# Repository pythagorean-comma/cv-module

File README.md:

# cv-module

Per-string CV generation for a six-string guitar effects box: six analogue VCAs
(SSI2164) set per-string levels, and the audio never enters the digital domain.

The module hangs off the six `RV{n}01` level-control positions of
[`summing-mixer`](../summing-mixer), replacing its per-channel trimmers. That
board is **fabricated**, so this repo consumes its interface at a pinned commit
and never writes to it — see [`contract/PINNED.md`](contract/PINNED.md).

```
6 x Nu capsule -> Nexus-GK -> summing-mixer ---- RV{n}01 socket ---- [this]
                                    ^                                  |
                                    +------------ SIN{n} --------------+
```

## Status

Green end to end. `verify.py` passes, `test_verify.py` catches all 112 planted
faults, DRC is at zero, no net is unrouted, and the fabrication package is
written.

| | |
|---|---|
| netlist | 290 parts, 185 nets, 825 pin connections |
| schematic | 0 merges, 0 breaks, 0 stranded pins; ERC clean, `ERC_ALLOWED` empty |
| board | 106.9 × 233.5 mm, 4 layers. 5114 segments, 1142 vias, one track width (0.2 mm), one via size (0.7/0.3), no signal copper on either reference plane |
| routing | every millimetre by KiCadRoutingTools via `krt.py` |
| section 5 constraints | checked mechanically; see `docs/constraints.md` |
| fixings | six, derived from `placement.mounting_deflection()`, each in a plane void |
| silkscreen | title block, connector legend generated from the netlist, 274 designators |
| fabrication package | `fab/` — 9 gerbers, drill, job file, CPL, `ORDER.md` |
| deferred blocks | none. `design.DEFERRED` and `design.UNSPECIFIED` are both empty |

Documents to look at: the [schematic](docs/cv-module-schematic.pdf), the
[layout](docs/cv-module-layout.pdf) one page per copper layer, and a
[render](docs/cv-module-top.png).

**Caveats worth knowing before ordering.** One capacitor is genuinely short on DC
bias — `C840` gives 1.65 µF at 12 V against TI's "2.2 µF or higher" and wants a
higher-voltage part in the same 1210 land. Three Murata lines have no bias curve
here and are reported unchecked. And no check in this repo opens a datasheet: the
netlist comparison is pad number against pin number, so a wrong package passes
everything — see [`footprint-audit.md`](docs/footprint-audit.md), which caught
three.

## Run it

Nothing to install. Stdlib only, following the mixer's own rule that "there is
no `requirements.txt` because there is nothing to install". KiCad 10 is not
optional: `verify.py` runs `kicad-cli` twice, `gen_pcb.py` needs its bundled
Python for `pcbnew`, and `gen_plots.py` plots the schematic, layout and render.

```bash
./build.sh
```

Regenerates the netlist, schematic, project, BOM, generated docs, plots and the
fabrication package, then verifies the board on disk. It never writes the board.
It checks for KiCad first and stops if it is missing; it does not check for
KiCadRoutingTools, because `krt.py` is not one of its stages.

### The three things that do write the board

None of these is in `build.sh`:

```bash
python3 gen_pcb.py --discard-routing   # place, pour and stitch, from nothing
python3 krt.py                         # route it; --commit keeps the result
python3 returns.py                     # add ground stitches; --commit writes
```

`gen_pcb.py` destroys all signal copper. It writes a fresh board with the
footprints placed and the planes poured and nothing else — use it to start again
from nothing, never to make a change. It refuses without `--discard-routing`.

`krt.py` writes a candidate, `out/cv-module-krt.kicad_pcb`; only `--commit`
touches the tracked board. Scope decides what it destroys: `--nets "ENVA*"`
re-lays those six and leaves the rest alone, a bare `python3 krt.py` re-lays
every net.

`returns.py` only adds ground stitches, so it cannot destroy anything. Re-run it
after any re-route. `mounts.py` and `silk.py` are the same shape.

**To move a netlist change onto the routed board**, use KiCad's **Tools → Update
PCB from Schematic** against `out/cv-module.kicad_sch`, which `build.sh`
regenerates. That is the only sync path.

### Toolchain notes

`krt.py` is the one thing here that is not stdlib-only, and it is a subprocess
for that reason — the tool needs numpy, scipy and shapely. Give it an interpreter
of its own, `~/code/KiCadRoutingTools/krt-venv` or `$KRT_PYTHON`; it refuses with
instructions if it cannot find one. See
[`routing-tool.md`](docs/routing-tool.md#installing-the-tools-dependencies).

`gen_pcb.py` re-runs itself under KiCad's bundled interpreter, because `pcbnew`
is a SWIG extension that exists nowhere else, then re-runs `gen_project.py` —
`SaveBoard()` rewrites the project file with KiCad's defaults and takes every
design rule with it.

`contract/socket.py` finds the mixer at `$SUMMING_MIXER`, then
`../summing-mixer`, then `~/code/summing-mixer`. **Keep the two as siblings,
never nested** — and never run `git` from a directory containing both.

## What this repo takes from the mixer, and what it does not

The mixer is a fabricated hardware interface this module references. Referencing
an interface does not mean importing another project's Python:

| | |
|---|---|
| **the interface** — `design.py`, `source.py`, `fab/mechanical-*.json` | read at the pinned commit through `contract/socket.py`, with `git show`. Never copied |
| **the KiCad plumbing** — `sexp` `kisch` `symlib` `kicad` `kisim` | copied into [`toolchain/`](toolchain/PROVENANCE.md). Ours, and modifiable |

The mixer's root is never on `sys.path`. `delta.py` expresses this module's
effect as a delta against the mixer's *own* model, which only works while that
model is the mixer's and not a fork of it.

## What is where

`CLAUDE.md` carries the working rules and the full repo layout. In short:
`design.py` holds the values, derivations and netlist; `verify.py` checks them
against KiCad's own export and `test_verify.py` proves those checks can fail;
`constraints.py` and `delta.py` ask whether the constraints have mechanisms and
what this module costs the existing design; `placement.py`, `krt.py`,
`returns.py`, `mounts.py` and `silk.py` are the board. `docs/` is what a person
reads; `out/` is what another tool reads; `fab/` is what a fabricator is given.

## Open

1. **`MEASURED["noise_floor"]`** — a meter on the mixer's mono output, and the
   only one of the three measurements that can be taken before this board
   exists. It is the most load-bearing unknown here: across its declared range
   the module costs **0.01 dB or 0.79 dB quiescent, 0.08 dB or 3.13 dB while the
   lead feature runs**. It also gates a component value — below 81 µV, `R_IN`
   should move from 12k1 to 7.5 kΩ. [`bench.md`](docs/bench.md).

2. **`MEASURED["mcu_dcdc_efficiency"]` and `["pico_smps_efficiency"]`** — two
   ammeters after fabrication. Confirmations rather than gates: floors of 53 %
   and 45 % against declared ranges starting at 75 and 86. Note that the board
   has no provision for the first — `VA_RAW` has no series element at U22's VIN,
   so that measurement needs a lifted pin or a fitted 0 Ω link. The second is
   free: `D806` is already in series with `VSYS`.

3. **The order form.** `fab/ORDER.md` lists what is not derivable from anything
   here: surface finish, mask and silkscreen colour, electrical test,
   panelisation, IPC class, quantity.

4. **Fiducials and test pads** — not fitted. Three fiducials are derived and
   costed; the test-point case is that no analogue rail and not `MAGND` itself
   has any probe point on the board.

5. **The south-east corner** is 57 mm from its nearest fixing and carries the
   USB socket. Grow the board, move the module, or accept it — all three are
   decisions, so `placement.mounting_reach()` reports the distance rather than
   taking one.

6. **Review the copper.** 844 router vias against an earlier seed's 595 is 33 %
   more perforations of both reference planes for 9.8 % less track. No check
   grades that trade. The recommendation is about scope: re-route a region, not
   the board.

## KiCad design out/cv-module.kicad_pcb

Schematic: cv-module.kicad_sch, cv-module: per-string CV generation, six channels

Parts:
C101, C201, C301, C401, C501, C601, C802, C814: 10u/16V X7R; C_1210_3225Metric
C102, C152, C202, C252, C302, C352, C402, C452, C502, C552, C602, C652: 1200p/50V C0G; C_0805_2012Metric
C121, C221, C321, C421, C521, C621: 100p/50V C0G; C_0805_2012Metric
C131, C231, C331, C431, C531, C631: 150n/50V X7R; C_0805_2012Metric
C141, C241, C341, C441, C541, C641: 56n/50V X7R; C_0805_2012Metric
C142, C242, C342, C442, C542, C642: 22n/50V X7R; C_0805_2012Metric
C151, C251, C351, C451, C551, C651, C810: 470n/50V X7R; C_0805_2012Metric
C701, C702, C703, C704, C705, C706, C707, C708, C709, C710, C711, C712, C713, C714, C715, C716, C717, C718, C719, C720, C721, C722, C723, C724, C803, C809, C817, C818, C819, C835, C836, C837, C838, C841, C842: 100n/50V X7R; C_0805_2012Metric
C801: 100n/50V C0G; C_0805_2012Metric
C805: 2n2/50V C0G; C_0805_2012Metric
C806, C815, C816: 1u/16V X7R; C_0805_2012Metric
C807, C808, C811, C812, C813: 10u/50V X7R; C_1210_3225Metric
C840: 2u2/50V X7R; C_1210_3225Metric
C843: 22u/16V X5R; C_1210_3225Metric
D151, D152, D251, D252, D351, D352, D451, D452, D551, D552, D651, D652, D805: 1N4148W; D_SOD-123
D801, D802, D813, D823, D833: BAT54; D_SOD-123
D803, D806: PMEG2010AEH; D_SOD-123F
D804: B340A; D_SMA
F801: 1.6A T 250V; Fuse_Schurter_UMT250
J1: CH1; PinHeader_1x02_P2.54mm_Vertical
J2: CH2; PinHeader_1x02_P2.54mm_Vertical
J3: CH3; PinHeader_1x02_P2.54mm_Vertical
J4: CH4; PinHeader_1x02_P2.54mm_Vertical
J5: CH5; PinHeader_1x02_P2.54mm_Vertical
J6: CH6; PinHeader_1x02_P2.54mm_Vertical
J7: BOND; TestPoint_Pad_D2.0mm
J8: PWR; PinHeader_1x02_P2.54mm_Vertical
J15: MIDIIN; PinHeader_1x03_P2.54mm_Vertical
J16: MIDIOUT; PinHeader_1x03_P2.54mm_Vertical
J17: TAP; PinHeader_1x02_P2.54mm_Vertical
J18: EXPR; PinHeader_1x03_P2.54mm_Vertical
J19: RESET; PinHeader_1x02_P2.54mm_Vertical
K801, K802, K803: DPDT
L801: 744222; L_CommonMode_Wuerth_WE-SL2
L802: 15u 20%; L_Bourns_SRN6045TA
Q801: DMG1012T; SOT-523
R101, R102, R201, R202, R301, R302, R401, R402, R501, R502, R601, R602, R801, R802: 10k 0.1%; R_0805_2012Metric
R111, R121, R211, R221, R311, R321, R411, R421, R511, R521, R611, R621: 12k1 0.1%; R_0805_2012Metric
R115, R215, R315, R415, R515, R615: 220R 1%; R_0805_2012Metric
R131, R132, R231, R232, R331, R332, R431, R432, R531, R532, R631, R632: 1M 1%; R_0805_2012Metric
R141, R144, R156, R241, R244, R256, R341, R344, R356, R441, R444, R456, R541, R544, R556, R641, R644, R656: 22k 1%; R_0805_2012Metric
R142, R143, R242, R243, R342, R343, R442, R443, R542, R543, R642, R643: 17k8 1%; R_0805_2012Metric
R151, R152, R153, R155, R251, R252, R253, R255, R351, R352, R353, R355, R451, R452, R453, R455, R551, R552, R553, R555, R651, R652, R653, R655, R830: 10k 1%; R_0805_2012Metric
R154, R157, R254, R257, R354, R357, R454, R457, R554, R557, R654, R657: 4k99 1%; R_0805_2012Metric
R803, R811, R812, R813, R814, R815, R816: 100k 1%; R_0805_2012Metric
R804, R805: 4R7 1%; R_0805_2012Metric
R827: 390R 1%; R_0805_2012Metric
R828: 33R 5%; R_0805_2012Metric
R829: 10R 5%; R_0805_2012Metric
R831, R832, R833: 1k 1%; R_0805_2012Metric
R850: 88k7 1%; R_0805_2012Metric
R851: 22k1 1%; R_0805_2012Metric
R901, R902: 0R; R_0805_2012Metric
U1, U2, U3, U4, U5, U6, U7, U8: OPA1644; SOIC-14_3.9x8.7mm_P1.27mm
U9, U10: SSI2164; SOIC-16_3.9x9.9mm_P1.27mm
U11: 74AHC541; SOIC-20W_7.5x12.8mm_P1.27mm
U12: MAX6126A25; SOIC-8_3.9x4.9mm_P1.27mm
U13, U14: TL074; SOIC-14_3.9x8.7mm_P1.27mm
U15: TMR6-2422WI; TRACO_TMR-6-xxxxWI_Dual_THT
U16: NCP1117-5.0; TO-252-2
U17: MCP3564; TSSOP-20_4.4x6.5mm_P0.65mm
U18: MCP1700-3.3; SOT-23
U19: RaspberryPi_Pico; RaspberryPi_Pico_SMD_HandSolder
U21: TLP2761; SO-6L_10x3.84mm_P1.27mm
U22: TPS560430XF; SOT-23-6

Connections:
AGND: J7.1, R901.2
AOUT1: D151.2 (A), D152.1 (K), U13.1
AOUT2: D251.2 (A), D252.1 (K), U13.7
AOUT3: D351.2 (A), D352.1 (K), U13.8
AOUT4: D451.2 (A), D452.1 (K), U13.14
AOUT5: D551.2 (A), D552.1 (K), U14.1
AOUT6: D651.2 (A), D652.1 (K), U14.7
BUF1: C101.1, R102.2, R151.1, R153.1, U1.1
BUF2: C201.1, R202.2, R251.1, R253.1, U1.7
BUF3: C301.1, R302.2, R351.1, R353.1, U1.8
BUF4: C401.1, R402.2, R451.1, R453.1, U1.14
BUF5: C501.1, R502.2, R551.1, R553.1, U2.1
BUF6: C601.1, R602.2, R651.1, R653.1, U2.7
CPL1: C101.2, R111.1
CPL2: C201.2, R211.1
CPL3: C301.2, R311.1
CPL4: C401.2, R411.1
CPL5: C501.2, R511.1
CPL6: C601.2, R611.1
CS: U17.13 (CS), U19.22 (GPIO17)
CVN1: C142.1, R143.2, U7.2 (-)
CVN2: C242.1, R243.2, U7.6 (-)
CVN3: C342.1, R343.2, U7.9 (-)
CVN4: C442.1, R443.2, U7.13 (-)
CVN5: C542.1, R543.2, U8.2 (-)
CVN6: C642.1, R643.2, U8.6 (-)
CVX1: C141.1, R141.2, R142.1, R143.1, R144.2
CVX2: C241.1, R241.2, R242.1, R243.1, R244.2
CVX3: C341.1, R341.2, R342.1, R343.1, R344.2
CVX4: C441.1, R441.2, R442.1, R443.1, R444.2
CVX5: C541.1, R541.2, R542.1, R543.1, R544.2
CVX6: C641.1, R641.2, R642.1, R643.1, R644.2
ENV1: C151.2, R155.2, R156.1, U2.8
ENV2: C251.2, R255.2, R256.1, U2.14
ENV3: C351.2, R355.2, R356.1, U4.8
ENV4: C451.2, R455.2, R456.1, U4.14
ENV5: C551.2, R555.2, R556.1, U6.8
ENV6: C651.2, R655.2, R656.1, U6.14
ENVA1: C152.1, R156.2, R157.1, U17.5 (CH0)
ENVA2: C252.1, R256.2, R257.1, U17.6 (CH1)
ENVA3: C352.1, R356.2, R357.1, U17.7 (CH2)
ENVA4: C452.1, R456.2, R457.1, U17.8 (CH3)
ENVA5: C552.1, R556.2, R557.1, U17.10 (CH5)
ENVA6: C652.1, R656.2, R657.1, U17.11 (CH6)
ENVN1: C151.1, R153.2, R154.2, R155.1, U2.9 (-)
ENVN2: C251.1, R253.2, R254.2, R255.1, U2.13 (-)
ENVN3: C351.1, R353.2, R354.2, R355.1, U4.9 (-)
ENVN4: C451.1, R453.2, R454.2, R455.1, U4.13 (-)
ENVN5: C551.1, R553.2, R554.2, R555.1, U6.9 (-)
ENVN6: C651.1, R653.2, R654.2, R655.1, U6.13 (-)
EXPR: C838.1, R833.2, U19.31 (GPIO26_ADC0)
EXPRV: J18.2, R832.2
EXPRW: J18.1, R833.1
FEN1: R101.2, R102.1, U1.2 (-)
FEN2: R201.2, R202.1, U1.6 (-)
FEN3: R301.2, R302.1, U1.9 (-)
FEN4: R401.2, R402.1, U1.13 (-)
FEN5: R501.2, R502.1, U2.2 (-)
FEN6: R601.2, R602.1, U2.6 (-)
FSAC: C805.2, D801.1 (K), D802.2 (A)
FSD: D813.2 (A), D823.2 (A), D833.2 (A), K801.12, K802.12, K803.12, Q801.3 (D)
FSDRV: C805.1, U19.20 (GPIO15)
FSG: C806.1, D802.1 (K), Q801.1 (G), R803.1
HW1: D152.2 (A), R152.2, R154.1
HW2: D252.2 (A), R252.2, R254.1
HW3: D352.2 (A), R352.2, R354.1
HW4: D452.2 (A), R452.2, R454.1
HW5: D552.2 (A), R552.2, R554.1
HW6: D652.2 (A), R652.2, R654.1
HWN1: D151.1 (K), R151.2, R152.1, U13.2 (-)
HWN2: D251.1 (K), R251.2, R252.1, U13.6 (-)
HWN3: D351.1 (K), R351.2, R352.1, U13.9 (-)
HWN4: D451.1 (K), R451.2, R452.1, U13.13 (-)
HWN5: D551.1 (K), R551.2, R552.1, U14.2 (-)
HWN6: D651.1 (K), R651.2, R652.1, U14.6 (-)
IGND: C807.2, C808.2, C809.2, C810.1, L801.3, U15.1 (-Vin), U15.3 (Remote)
IGND_J: J8.2, L801.2
IIN1: R111.2, R115.1, U9.2 (I_IN1)
IIN2: R211.2, R215.1, U9.7 (I_IN2)
IIN3: R311.2, R315.1, U9.10 (I_IN3)
IIN4: R411.2, R415.1, U10.2 (I_IN1)
IIN5: R511.2, R515.1, U10.7 (I_IN2)
IIN6: R611.2, R615.1, U10.10 (I_IN3)
IOUT1: C121.1, R121.1, R132.2, U3.2 (-), U9.4 (I_OUT1)
IOUT2: C221.1, R221.1, R232.2, U3.6 (-), U9.5 (I_OUT2)
IOUT3: C321.1, R321.1, R332.2, U3.9 (-), U9.12 (I_OUT3)
IOUT4: C421.1, R421.1, R432.2, U3.13 (-), U10.4 (I_OUT1)
IOUT5: C521.1, R521.1, R532.2, U4.2 (-), U10.5 (I_OUT2)
IOUT6: C621.1, R621.1, R632.2, U4.6 (-), U10.12 (I_OUT3)
IRQ: U17.17 (IRQ), U19.26 (GPIO20)
IVOUT1: C121.2, K801.8, R121.2, R131.1, U3.1
IVOUT2: C221.2, K801.5, R221.2, R231.1, U3.7
IVOUT3: C321.2, K802.8, R321.2, R331.1, U3.8
IVOUT4: C421.2, K802.5, R421.2, R431.1, U3.14
IVOUT5: C521.2, K803.8, R521.2, R531.1, U4.1
IVOUT6: C621.2, K803.5, R621.2, R631.1, U4.7
LOGO1: R141.1, U11.18 (Y0)
LOGO2: R241.1, U11.17 (Y1)
LOGO3: R341.1, U11.16 (Y2)
LOGO4: R441.1, U11.15 (Y3)
LOGO5: R541.1, U11.14 (Y4)
LOGO6: R641.1, U11.13 (Y5)
MAGND: C102.2, C141.2, C152.2, C202.2, C241.2, C252.2, C302.2, C341.2, C352.2, C402.2, C441.2, C452.2, C502.2, C541.2, C552.2, C602.2, C641.2, C652.2, C701.2, C702.2, C703.2, C704.2, C705.2, C706.2, C707.2, C708.2, C709.2, C710.2, C711.2, C712.2, C713.2, C714.2, C715.2, C716.2, C717.2, C718.2, C719.2, C720.2, C721.2, C722.2, C723.2, C724.2, C801.2, C802.2, C803.2, C815.2, C816.2, C817.2, C818.2, C819.2, D803.1 (K), R157.2, R257.2, R357.2, R457.2, R557.2, R657.2, R901.1, R902.1, U1.3 (+), U1.5 (+), U1.10 (+), U1.12 (+), U2.3 (+), U2.5 (+), U2.10 (+), U2.12 (+), U3.3 (+), U3.5 (+), U3.10 (+), U3.12 (+), U4.3 (+), U4.5 (+), U4.10 (+), U4.12 (+), U5.3 (+), U5.5 (+), U5.10 (+), U5.12 (+), U6.3 (+), U6.5 (+), U6.10 (+), U6.12 (+), U7.3 (+), U7.5 (+), U7.10 (+), U7.12 (+), U8.3 (+), U8.5 (+), U8.10 (+), U8.12 (+), U9.8 (GND), U9.13 (I_OUT4), U9.15 (I_IN4), U10.8 (GND), U10.13 (I_OUT4), U10.15 (I_IN4), U11.8 (A6), U11.9 (A7), U11.10 (GND), U12.3 (GND), U12.4 (GNDS), U13.3 (+), U13.5 (+), U13.10 (+), U13.12 (+), U14.3 (+), U14.5 (+), U14.10 (+), U14.12 (+), U17.2 (AGND), U17.3 (REFIN-), U17.9 (CH4), U17.12 (CH7), U17.19 (DGND), U18.1 (GND)
MCB: C842.1, U22.1 (CB)
MCLK: U17.18 (MCLK), U19.27 (GPIO21)
MDGND: C806.2, C810.2, C811.2, C812.2, C813.2, C814.2, C835.2, C836.2, C837.2, C838.2, C840.2, C841.2, C843.2, D801.2 (A), J16.2, J17.2, J18.3, J19.2, Q801.2 (S), R803.2, R811.2, R812.2, R813.2, R814.2, R815.2, R816.2, R851.2, R902.2, U15.7 (Com), U16.1 (GND), U19.3 (GND), U19.8 (GND), U19.13 (GND), U19.18 (GND), U19.23 (GND), U19.28 (GND), U19.33 (AGND), U19.38 (GND), U21.4 (GND), U22.2 (GND)
MFB: R850.2, R851.1, U22.3 (FB)
MIDI_RX: U19.17 (GPIO13), U21.5 (VO)
MIDI_TX: R829.1, U19.16 (GPIO12)
MINA: D805.1 (K), R827.2, U21.1 (A)
MINJ: J15.1, R827.1
MINK: D805.2 (A), J15.3, U21.3 (K)
MINSH: C836.1, J15.2
MISO: U17.16 (SDO), U19.21 (GPIO16)
MOSI: U17.15 (SDI), U19.25 (GPIO19)
MOUTD: J16.3, R829.2
MOUTV: J16.1, R828.2
MSW: C842.2, L802.1, U22.6 (SW)
OE: U11.1 (G1), U11.19 (G2), U19.19 (GPIO14)
PIN1: J1.1, K801.10, R101.1
PIN2: J2.1, K801.3, R201.1
PIN3: J3.1, K802.10, R301.1
PIN4: J4.1, K802.3, R401.1
PIN5: J5.1, K803.10, R501.1
PIN6: J6.1, K803.3, R601.1
PWM1: R811.1, U11.2 (A0), U19.1 (GPIO0)
PWM2: R812.1, U11.3 (A1), U19.4 (GPIO2)
PWM3: R813.1, U11.4 (A2), U19.6 (GPIO4)
PWM4: R814.1, U11.5 (A3), U19.9 (GPIO6)
PWM5: R815.1, U11.6 (A4), U19.11 (GPIO8)
PWM6: R816.1, U11.7 (A5), U19.14 (GPIO10)
RCJ1: C102.1, R115.2
RCJ2: C202.1, R215.2
RCJ3: C302.1, R315.2
RCJ4: C402.1, R415.2
RCJ5: C502.1, R515.2
RCJ6: C602.1, R615.2
RINV: R801.2, R802.1, U8.9 (-)
RUN: J19.1, U19.30 (RUN)
SCLK: U17.14 (SCK), U19.24 (GPIO18)
SIN1: J1.2, K801.9
SIN2: J2.2, K801.4
SIN3: J3.2, K802.9
SIN4: J4.2, K802.4
SIN5: J5.2, K803.9
SIN6: J6.2, K803.4
SPARE0: U8.13 (-), U8.14
SPARE1: U14.8, U14.9 (-)
SPARE2: U14.13 (-), U14.14
SRV1: C131.2, R132.1, U5.1
SRV2: C231.2, R232.1, U5.7
SRV3: C331.2, R332.1, U5.8
SRV4: C431.2, R432.1, U5.14
SRV5: C531.2, R532.1, U6.1
SRV6: C631.2, R632.1, U6.7
SVN1: C131.1, R131.2, U5.2 (-)
SVN2: C231.1, R231.2, U5.6 (-)
SVN3: C331.1, R331.2, U5.9 (-)
SVN4: C431.1, R431.2, U5.13 (-)
SVN5: C531.1, R531.2, U6.2 (-)
SVN6: C631.1, R631.2, U6.6 (-)
TAP: C837.1, R831.2, U19.29 (GPIO22)
TAPJ: J17.1, R830.2, R831.1
V3V3: C816.1, C817.1, C818.1, U17.1 (AVDD), U17.20 (DVDD), U18.2 (VO)
V5: C814.1, C815.1, U12.2 (IN), U16.2 (VO), U18.3 (VI)
VA+: C701.1, C703.1, C705.1, C707.1, C709.1, C711.1, C713.1, C715.1, C717.1, C719.1, C721.1, C723.1, C811.1, R804.2, U1.4 (V+), U2.4 (V+), U3.4 (V+), U4.4 (V+), U5.4 (V+), U6.4 (V+), U7.4 (V+), U8.4 (V+), U9.16 (V+), U10.16 (V+), U13.4 (V+), U14.4 (V+)
VA-: C702.1, C704.1, C706.1, C708.1, C710.1, C712.1, C714.1, C716.1, C718.1, C720.1, C722.1, C724.1, C812.1, R805.2, U1.11 (V-), U2.11 (V-), U3.11 (V-), U4.11 (V-), U5.11 (V-), U6.11 (V-), U7.11 (V-), U8.11 (V-), U9.9 (V-), U10.9 (V-), U13.11 (V-), U14.11 (V-)
VA_RAW: C813.1, C840.1, C841.1, R804.1, U15.6 (+Vout), U16.3 (VI), U22.4 (EN), U22.5 (VIN)
VC1: C142.2, R142.2, U7.1, U9.3 (VC1)
VC2: C242.2, R242.2, U7.7, U9.6 (VC2)
VC3: C342.2, R342.2, U7.8, U9.11 (VC3)
VC4: C442.2, R442.2, U7.14, U10.3 (VC1)
VC5: C542.2, R542.2, U8.1, U10.6 (VC2)
VC6: C642.2, R642.2, U8.7, U10.11 (VC3)
VIN: D804.2 (A), L801.4
VIN_F: F801.2, L801.1
VIN_J: F801.1, J8.1
VIN_P: C807.1, C808.1, C809.1, D804.1 (K), U15.2 (+Vin)
VMCU: C835.1, R828.1, R830.1, R832.1, U19.36 (3V3), U21.6 (VDD)
VMOD: C843.1, D806.2 (A), D813.1 (K), D823.1 (K), D833.1 (K), K801.1, K802.1, K803.1, L802.2, R850.1
VNR: C801.1, U12.1 (NR)
VN_RAW: R805.1, U15.8 (-Vout)
VREF: C802.1, C803.1, C819.1, R801.1, U11.20 (VCC), U12.6 (OUTS), U12.7 (OUTF), U17.4 (REFIN+)
VREFN: D803.2 (A), R144.1, R244.1, R344.1, R444.1, R544.1, R644.1, R802.2, U8.8
VSYS: D806.1 (K), U19.39 (VSYS)

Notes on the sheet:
The boundary runs through U11: A-side from the digital domain, Y-side precision analogue, GND on MAGND. See floorplan.py.
Fail-safe: any stuck MCU state collapses the pump, the FET releases, and de-energised is bypass. D803 covers the one path the pump cannot see. See design.fail_safe().
R901 is THE bond, to the mixer's TP6. R902 is internal. Constraint 2 allows exactly one of the first.
The isolation barrier runs through U15: pins 1-3 are referenced to IGND, which is the inlet's 0 V and the mixer's PGND through the shared jack; pins 6-8 to MDGND. C810 is the only other part that touches both. See design.barrier_return().
The envelope ADC. AGND and DGND are one net here and both are MAGND -- DS20006181C section 7.3's second scheme, and the only one compatible with this board having exactly one analogue/digital star. Six logic signals leave for the controller and no analogue trace crosses the boundary; MCLK is one of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
The controller. Three 3.3 V and 5 V nets on this sheet and no two of them are one: V3V3 is the ADC's, linear from V5; VMOD is U22's switched 5 V, carrying the module and the relay coils; VMCU is the module's own 3.3 V, made on it by an RT6150 out of VSYS and brought back out on pin 36. V5 is what i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

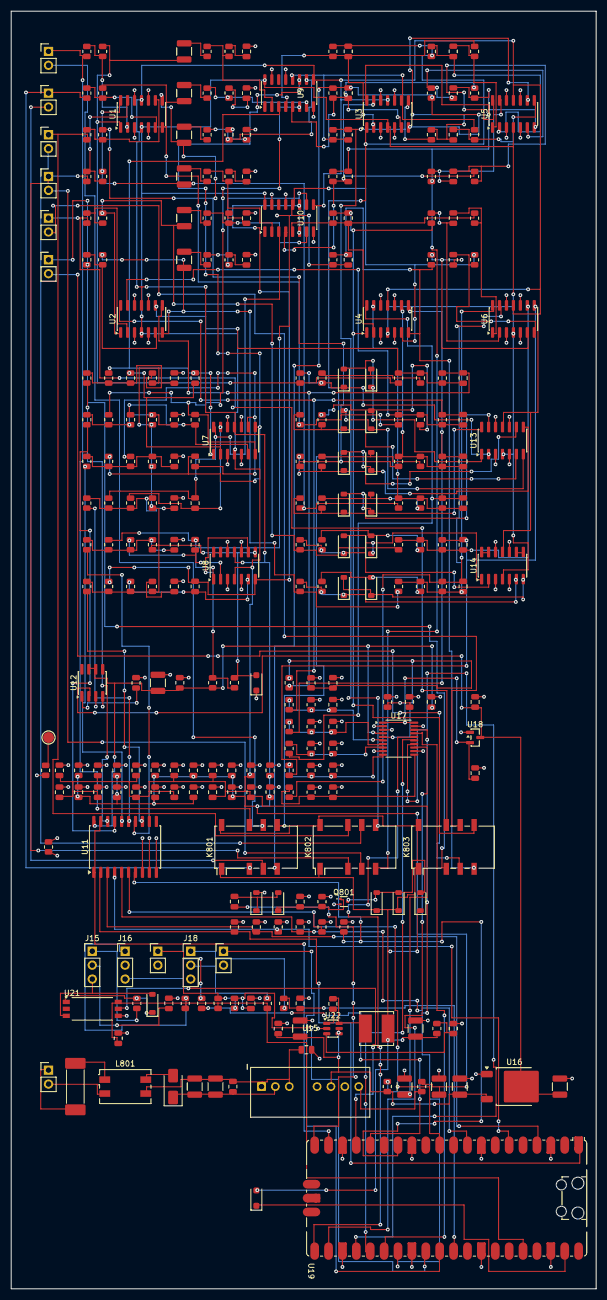
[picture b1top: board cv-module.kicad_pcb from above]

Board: 4 copper layers, 106.9 x 233.6 mm, 290 parts (0 on the bottom side), 185 nets.

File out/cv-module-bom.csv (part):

Reference,Value,Footprint,MPN,Fitted,Order,Unit low,Unit high,Currency,Qty break,Basis,Source
"C101,C201,C301,C401,C501,C601,C802,C814",10u/16V X7R,Capacitor_SMD:C_1210_3225Metric,GRM21BR61C106KE15L,8,12,0.08,0.25,GBP,25,band,"typical distributor band, not read this session"
"C102,C152,C202,C252,C302,C352,C402,C452,C502,C552,C602,C652",1200p/50V C0G,Capacitor_SMD:C_0805_2012Metric,GRM2165C1H122JA01D,12,16,0.02,0.08,GBP,100,band,"typical distributor band, not read this session"
"C121,C221,C321,C421,C521,C621",100p/50V C0G,Capacitor_SMD:C_0805_2012Metric,GRM2165C1H101JA01D,6,10,0.02,0.08,GBP,100,band,"typical distributor band, not read this session"
"C131,C231,C331,C431,C531,C631",150n/50V X7R,Capacitor_SMD:C_0805_2012Metric,GRM216R71H154KA01D,6,10,0.02,0.08,GBP,100,band,"typical distributor band, not read this session"
"C141,C241,C341,C441,C541,C641",56n/50V X7R,Capacitor_SMD:C_0805_2012Metric,GRM216R71H563KA01D,6,10,0.02,0.08,GBP,100,band,"typical distributor band, not read this session"
"C142,C242,C342,C442,C542,C642",22n/50V X7R,Capacitor_SMD:C_0805_2012Metric,GRM216R71H223KA01D,6,10,0.02,0.08,GBP,100,band,"typical distributor band, not read this session"
"C151,C251,C351,C451,C551,C651,C810",470n/50V X7R,Capacitor_SMD:C_0805_2012Metric,GRM21BR71H474KA88L,7,11,0.02,0.08,GBP,100,band,"typical distributor band, not read this session"
"C701,C702,C703,C704,C705,C706,C707,C708,C709,C710,C711,C712,C713,C714,C715,C716,C717,C718,C719,C720,C721,C722,C723,C724,C803,C809,C817,C818,C819,C835,C836,C837,C838,C841,C842",100n/50V X7R,Capacitor_SMD:C_0805_2012Metric,GRM216R71H104KA01D,35,39,0.01,0.05,GBP,100,band,"typical distributor band, not read this session"
C801,100n/50V C0G,Capacitor_SMD:C_0805_2012Metric,GRM2195C1H104JA01D,1,5,0.15,0.45,GBP,10,band,"typical distributor band, not read this session"
C805,2n2/50V C0G,Capacitor_SMD:C_0805_2012Metric,GRM2165C1H222JA01D,1,5,0.02,0.08,GBP,100,band,"typical distributor band, not read this session"
"C806,C815,C816",1u/16V X7R,Capacitor_SMD:C_0805_2012Metric,GRM21BR71C105KA01L,3,7,0.02,0.08,GBP,100,band,"typical distributor band, not read this session"
"C807,C808,C811,C812,C813",10u/50V X7R,Capacitor_SMD:C_1210_3225Metric,GRM32ER71H106KA12L,5,9,0.30,0.80,GBP,25,band,"typical distributor band, not read this session"
C840,2u2/50V X7R,Capacitor_SMD:C_1210_3225Metric,GRM21BR71H225KA73L,1,5,0.05,0.20,GBP,25,band,"typical distributor band, not read this session"
C843,22u/16V X5R,Capacitor_SMD:C_1210_3225Metric,GRM21BR61C226ME44L,1,5,0.08,0.30,GBP,25,band,"typical distributor band, not read this session"
"D151,D152,D251,D252,D351,D352,D451,D452,D551,D552,D651,D652,D805",1N4148W,Diode_SMD:D_SOD-123,1N4148WS-7-F,13,14,0.02,0.08,GBP,100,band,"typical distributor band, not read this session"
"D801,D802,D813,D823,D833",BAT54,Diode_SMD:D_SOD-123,BAT54-7-F,5,6,0.05,0.15,GBP,100,band,"typical distributor band, not read this session"
"D803,D806",PMEG2010AEH,Diode_SMD:D_SOD-123F,"PMEG2010AEH,115",2,3,0.10,0.30,GBP,100,band,"typical distributor band, not read this session"
D804,B340A,Diode_SMD:D_SMA,B340A-13-F,1,5,0.20,0.60,GBP,10,band,"typical distributor band, not read this session"
F801,1.6A T 250V,Fuse:Fuse_Schurter_UMT250,3403.0168.11,1,5,1.80,1.80,USD,1,read,https://www.digikey.com/en/products/detail/schurter-inc/3403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
J1,CH1,Connector_PinHeader_2.54mm:PinHeader_1x02_P2.54mm_Vertical,61300211121,1,5,0.25,0.60,GBP,10,band,"typical distributor band, not read this session"
J2,CH2,Connector_PinHeader_2.54mm:PinHeader_1x02_P2.54mm_Vertical,61300211121,1,5,0.25,0.60,GBP,10,band,"typical distributor band, not read this session"
J3,CH3,Connector_PinHeader_2.54mm:PinHeader_1x02_P2.54mm_Vertical,61300211121,1,5,0.25,0.60,GBP,10,band,"typical distributor band, not read this session"
J4,CH4,Connector_PinHeader_2.54mm:PinHeader_1x02_P2.54mm_Vertical,61300211121,1,5,0.25,0.60,GBP,10,band,"typical distributor band, not read this session"
J5,CH5,Connector_PinHeader_2.54mm:PinHeader_1x02_P2.54mm_Vertical,61300211121,1,5,0.25,0.60,GBP,10,band,"typical distributor band, not read this session"
J6,CH6,Connector_PinHeader_2.54mm:PinHeader_1x02_P2.54mm_Vertical,61300211121,1,5,0.25,0.60,GBP,10,band,"typical distributor band, not read this session"
J8,PWR,Connector_PinHeader_2.54mm:PinHeader_1x02_P2.54mm_Vertical,61300211121,1,5,0.25,0.60,GBP,10,band,"typical distributor band, not read this session"
J15,MIDIIN,Connector_PinHeader_2.54mm:PinHeader_1x03_P2.54mm_Vertical,61300311121,1,5,0.30,0.75,GBP,10,band,"typical distributor band, not read this session"
J16,MIDIOUT,Connector_PinHeader_2.54mm:PinHeader_1x03_P2.54mm_Vertical,61300311121,1,5,0.30,0.75,GBP,10,band,"typical distributor band, not read this session"
J17,TAP,Connector_PinHeader_2.54mm:PinHeader_1x02_P2.54mm_Vertical,61300211121,1,5,0.25,0.60,GBP,10,band,"typical distributor band, not read this session"
J18,EXPR,Connector_PinHeader_2.54mm:PinHeader_1x03_P2.54mm_Vertical,61300311121,1,5,0.30,0.75,GBP,10,band,"typical distributor band, not read this session"
J19,RESET,Connector_PinHeader_2.54mm:PinHeader_1x02_P2.54mm_Vertical,61300211121,1,5,0.25,0.60,GBP,10,band,"typical distributor band, not read this session"
"K801,K802,K803",G6S-2 DC5,Relay_SMD:Relay_DPDT_Omron_G6S-2F,G6S-2 DC5,3,7,3.00,5.50,GBP,10,band,"typical distributor band, not read this session"
L801,744222,Inductor_SMD:L_CommonMode_Wuerth_WE-SL2,744222,1,5,1.97,1.97,GBP,1,read,https://www.digikey.co.uk/en/products/detail/w%C3%BCrth-elek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
L802,15u 20%,Inductor_SMD:L_Bourns_SRN6045TA,SRN6045TA-150M,1,5,0.30,0.90,GBP,25,band,"typical distributor band, not read this session"
Q801,DMG1012T,Package_TO_SOT_SMD:SOT-523,DMG1012T-7,1,2,0.06,0.20,GBP,100,band,"typical distributor band, not read this session"
"R101,R102,R201,R202,R301,R302,R401,R402,R501,R502,R601,R602,R801,R802",10k 0.1%,Resistor_SMD:R_0805_2012Metric,ERA6AEB103V,14,18,0.10,0.30,GBP,100,band,"typical distributor band, not read this session"
"R111,R121,R211,R221,R311,R321,R411,R421,R511,R521,R611,R621",12k1 0.1%,Resistor_SMD:R_0805_2012Metric,ERA6AEB1212V,12,16,0.10,0.30,GBP,25,band,"typical distributor band, not read this session"
"R115,R215,R315,R415,R515,R615",220R 1%,Resistor_SMD:R_0805_2012Metric,RC0805FR-07220RL,6,10,0.01,0.03,GBP,100,band,"typical distributor band, not read this session"
"R131,R132,R231,R232,R331,R332,R431,R432,R531,R532,R631,R632",1M 1%,Resistor_SMD:R_0805_2012Metric,RC0805FR-071ML,12,16,0.01,0.03,GBP,100,band,"typical distributor band, not read this session"
"R141,R144,R156,R241,R244,R256,R341,R344,R356,R441,R444,R456,R541,R544,R556,R641,R644,R656",22k 1%,Resistor_SMD:R_0805_2012Metric,RC0805FR-0722KL,18,22,0.01,0.03,GBP,100,band,"typical distributor band, not read this session"
"R142,R143,R242,R243,R342,R343,R442,R443,R542,R543,R642,R643",17k8 1%,Resistor_SMD:R_0805_2012Metric,RC0805FR-0717K8L,12,16,0.01,0.03,GBP,100,band,"typical distributor band, not read this session"
"R151,R152,R153,R155,R251,R252,R253,R255,R351,R352,R353,R355,R451,R452,R453,R455,R551,R552,R553,R555,R651,R652,R653,R655,R830",10k 1%,Resistor_SMD:R_0805_2012Metric,RC0805FR-0710KL,25,29,0.01,0.03,GBP,100,band,"typical distributor band, not read this session"
"R154,R157,R254,R257,R354,R357,R454,R457,R554,R557,R654,R657",4k99 1%,Resistor_SMD:R_0805_2012Metric,RC0805FR-074K99L,12,16,0.01,0.03,GBP,100,band,"typical distributor band, not read this session"
"R803,R811,R812,R813,R814,R815,R816",100k 1%,Resistor_SMD:R_0805_2012Metric,RC0805FR-07100KL,7,11,0.01,0.03,GBP,100,band,"typical distributor band, not read this session"
"R804,R805",4R7 1%,Resistor_SMD:R_0805_2012Metric,RC0805FR-074R7L,2,6,0.01,0.03,GBP,100,band,"typical distributor band, not read this session"
R827,390R 1%,Resistor_SMD:R_0805_2012Metric,RC0805FR-07390RL,1,5,0.01,0.05,GBP,100,band,"typical distributor band, not read this session"
R828,33R 5%,Resistor_SMD:R_0805_2012Metric,RC0805JR-0733RL,1,5,0.01,0.05,GBP,100,band,"typical distributor band, not read this session"
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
